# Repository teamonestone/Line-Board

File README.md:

# Line-Board
A CNY-70 based Line Sensor Board

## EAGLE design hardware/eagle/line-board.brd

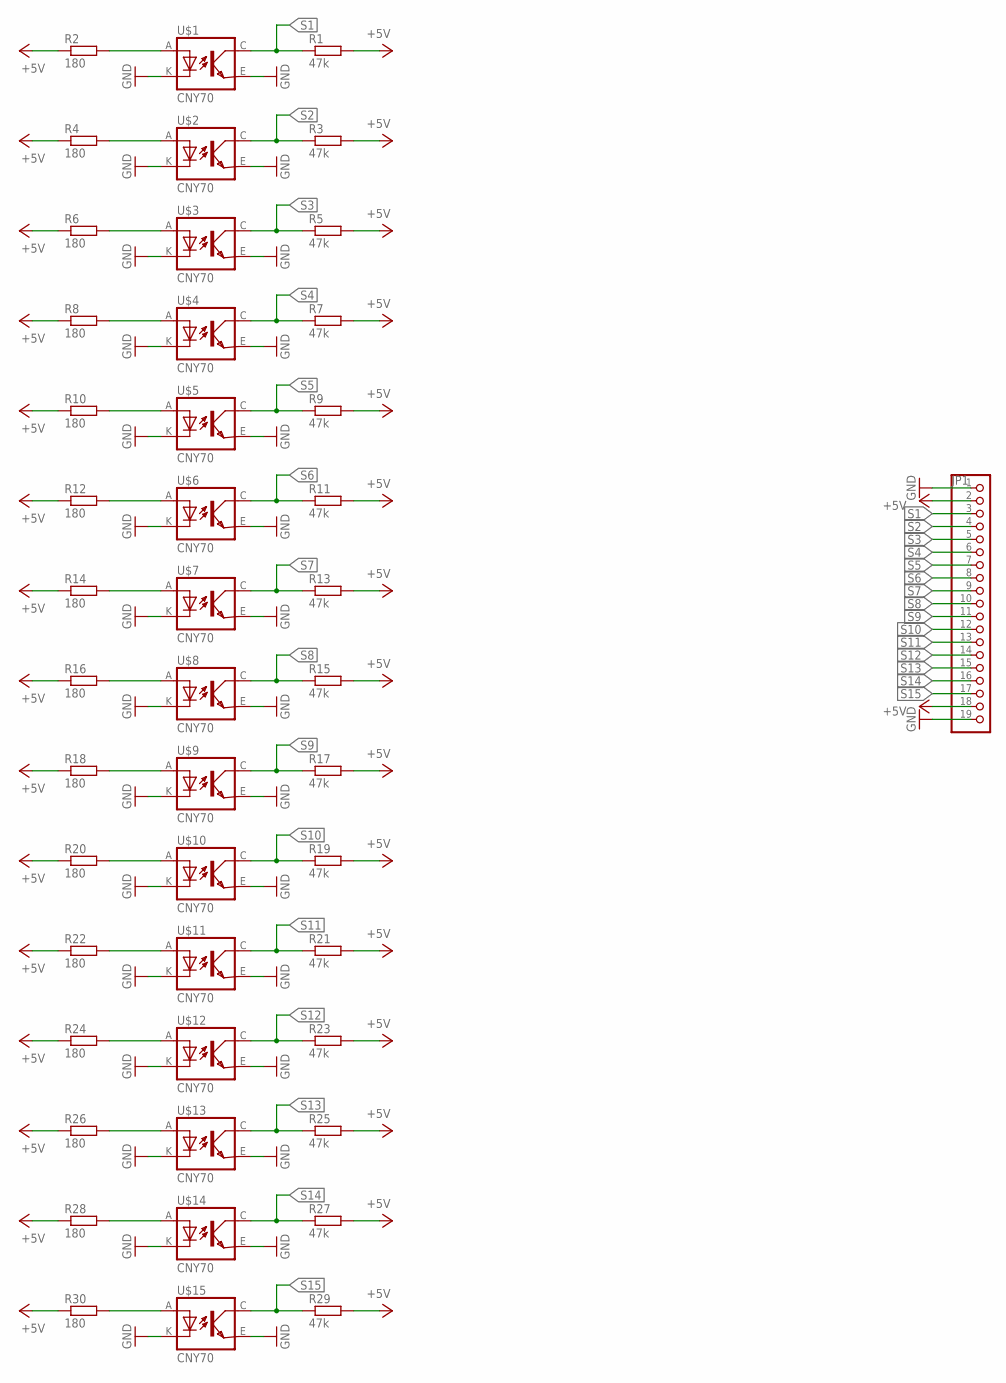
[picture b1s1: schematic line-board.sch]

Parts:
JP1: PINHD-1X19; 1X19
R1, R3, R5, R7, R9, R11, R13, R15, R17, R19, R21, R23, R25, R27, R29: 47k; R1206
R2, R4, R6, R8, R10, R12, R14, R16, R18, R20, R22, R24, R26, R28, R30: 180; R1206
U$1, U$2, U$3, U$4, U$5, U$6, U$7, U$8, U$9, U$10, U$11, U$12, U$13, U$14, U$15: CNY70; 4

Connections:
+5V: JP1.2, JP1.18, R1.2, R2.1, R3.2, R4.1, R5.2, R6.1, R7.2, R8.1, R9.2, R10.1, R11.2, R12.1, R13.2, R14.1, R15.2, R16.1, R17.2, R18.1, R19.2, R20.1, R21.2, R22.1, R23.2, R24.1, R25.2, R26.1, R27.2, R28.1, R29.2, R30.1
GND: JP1.1, JP1.19, U$1.E (EMI), U$1.K (C), U$2.E (EMI), U$2.K (C), U$3.E (EMI), U$3.K (C), U$4.E (EMI), U$4.K (C), U$5.E (EMI), U$5.K (C), U$6.E (EMI), U$6.K (C), U$7.E (EMI), U$7.K (C), U$8.E (EMI), U$8.K (C), U$9.E (EMI), U$9.K (C), U$10.E (EMI), U$10.K (C), U$11.E (EMI), U$11.K (C), U$12.E (EMI), U$12.K (C), U$13.E (EMI), U$13.K (C), U$14.E (EMI), U$14.K (C), U$15.E (EMI), U$15.K (C)
unnamed: R24.2, U$12.A
unnamed: R2.2, U$1.A
unnamed: R4.2, U$2.A
unnamed: R26.2, U$13.A
unnamed: R6.2, U$3.A
unnamed: R28.2, U$14.A
unnamed: R8.2, U$4.A
unnamed: R30.2, U$15.A
unnamed: R10.2, U$5.A
unnamed: R12.2, U$6.A
unnamed: R14.2, U$7.A
unnamed: R16.2, U$8.A
unnamed: R18.2, U$9.A
unnamed: R20.2, U$10.A
unnamed: R22.2, U$11.A
S1: JP1.3, R1.1, U$1.C (COL)
S2: JP1.4, R3.1, U$2.C (COL)
S3: JP1.5, R5.1, U$3.C (COL)
S4: JP1.6, R7.1, U$4.C (COL)
S5: JP1.7, R9.1, U$5.C (COL)
S6: JP1.8, R11.1, U$6.C (COL)
S7: JP1.9, R13.1, U$7.C (COL)
S8: JP1.10, R15.1, U$8.C (COL)
S9: JP1.11, R17.1, U$9.C (COL)
S10: JP1.12, R19.1, U$10.C (COL)
S11: JP1.13, R21.1, U$11.C (COL)
S12: JP1.14, R23.1, U$12.C (COL)
S13: JP1.15, R25.1, U$13.C (COL)
S14: JP1.16, R27.1, U$14.C (COL)
S15: JP1.17, R29.1, U$15.C (COL)

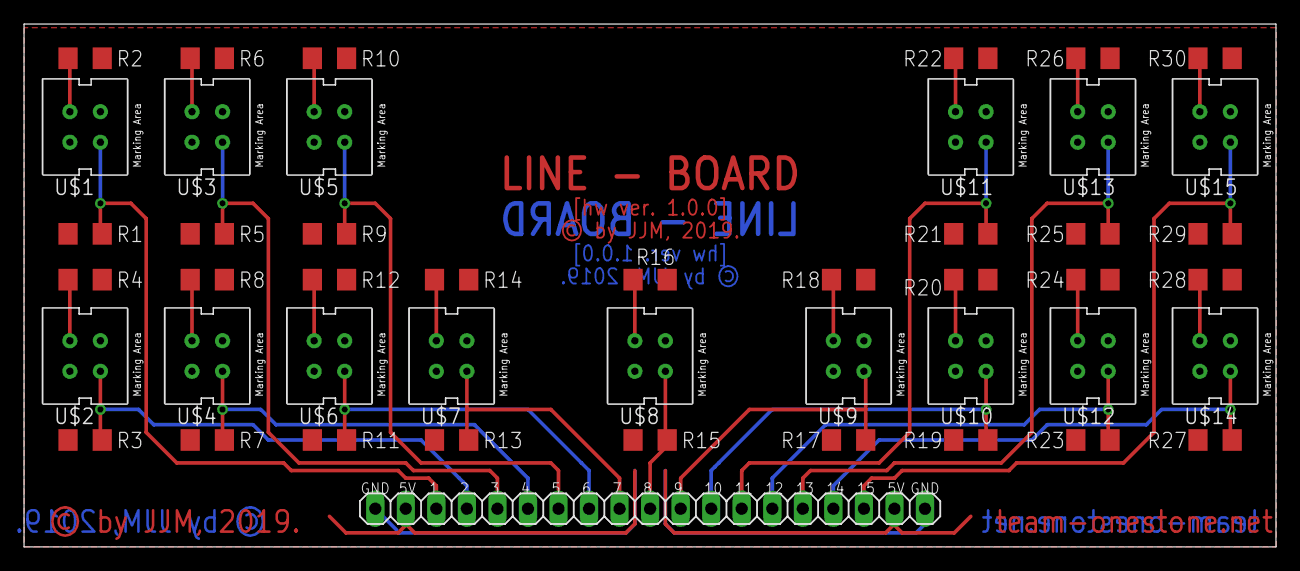
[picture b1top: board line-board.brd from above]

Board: 2 copper layers, 104.1 x 43.5 mm, 46 parts (0 on the bottom side), 32 nets.

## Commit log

2019-10-15 gitignore
2019-10-15 basic layout
2019-10-15 layout
2019-10-15 hw version 1.0.0

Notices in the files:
hardware/eagle/line-board.brd:
© by JJM, 2019.
